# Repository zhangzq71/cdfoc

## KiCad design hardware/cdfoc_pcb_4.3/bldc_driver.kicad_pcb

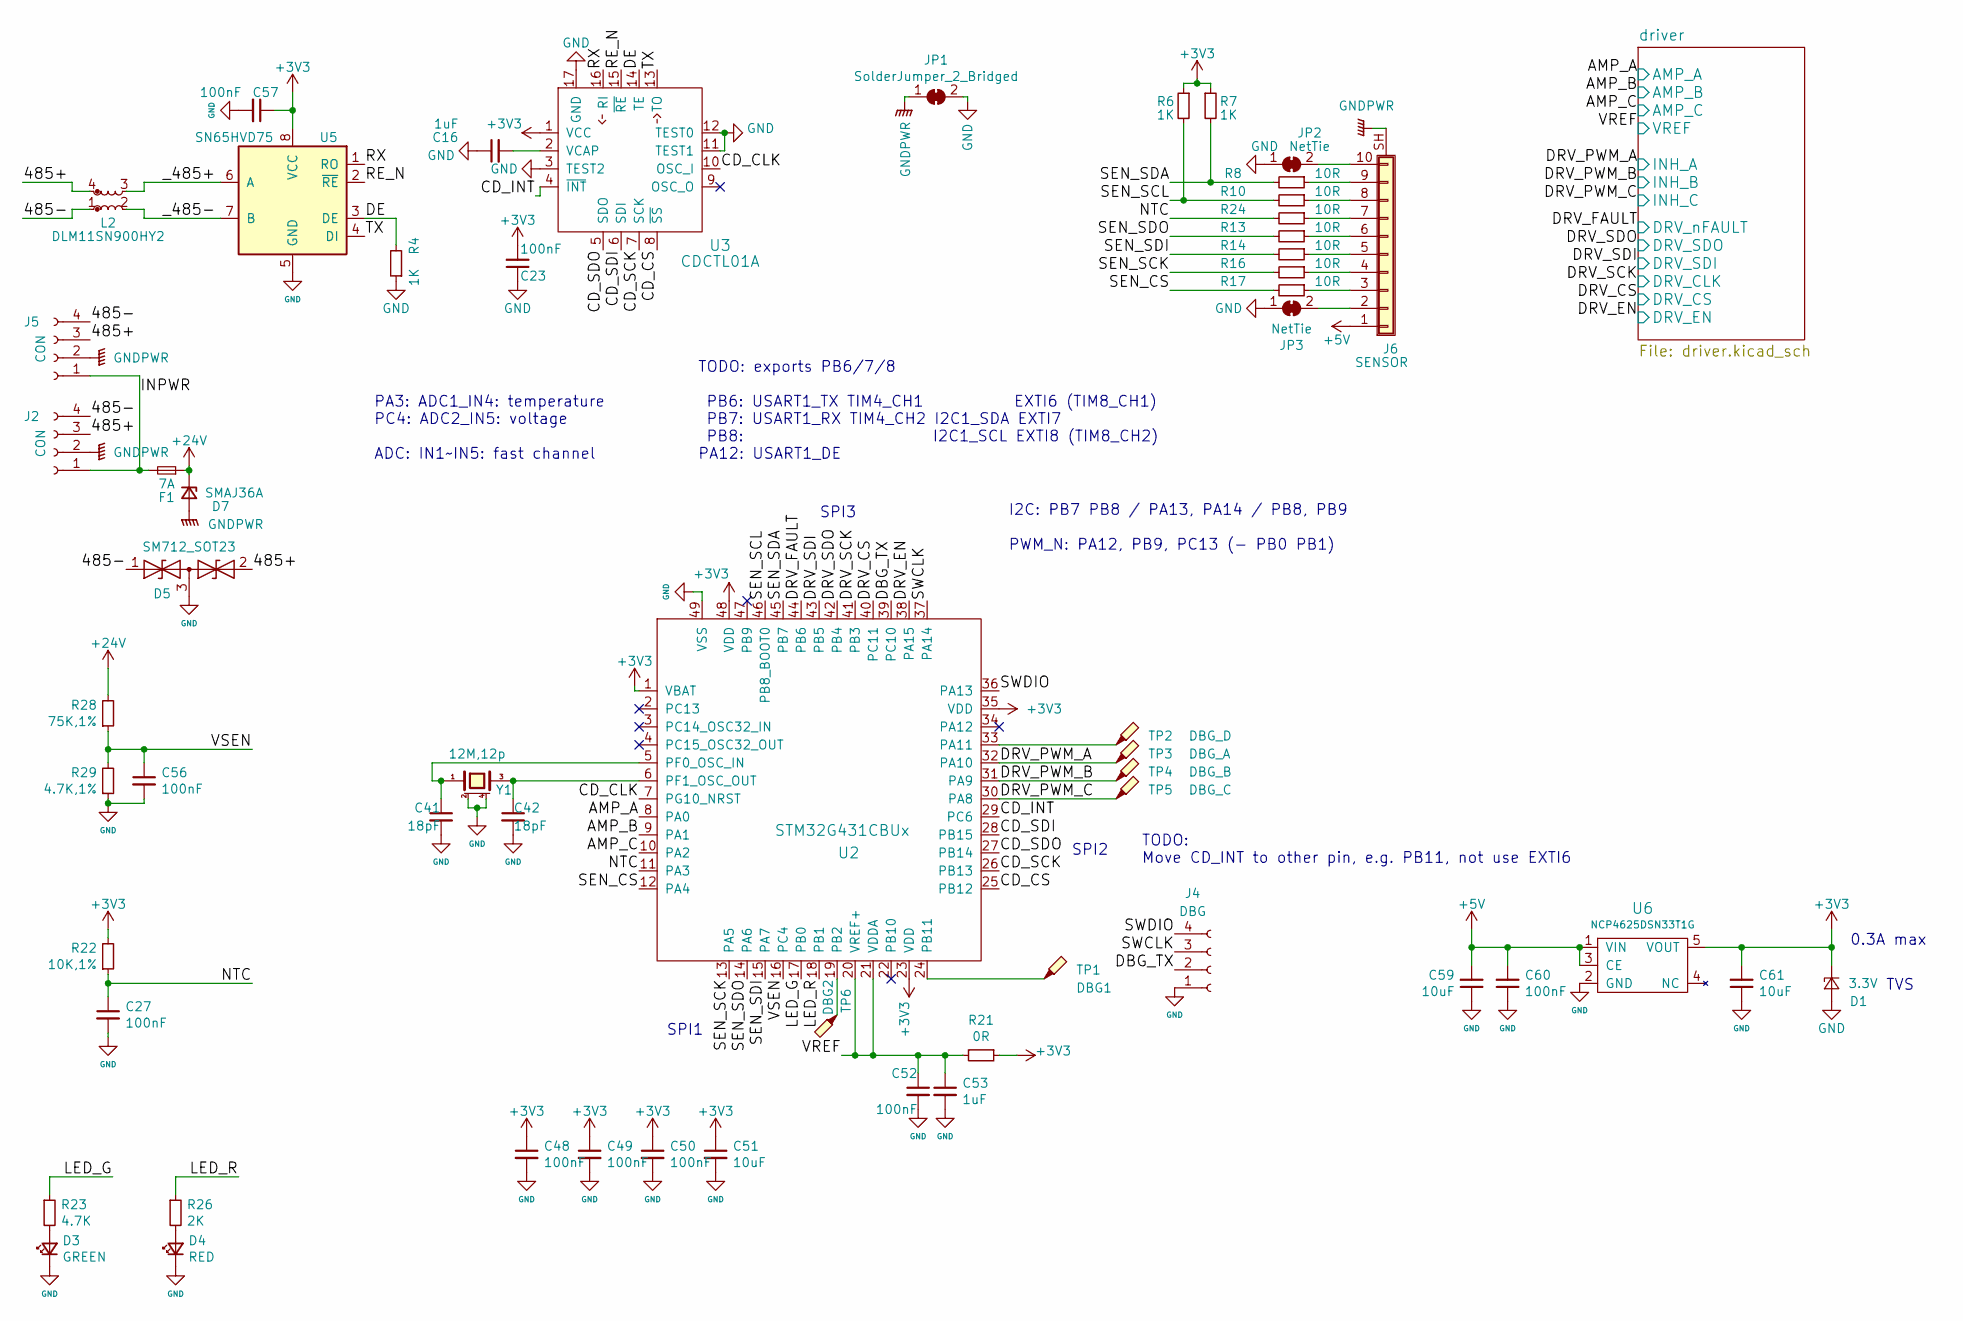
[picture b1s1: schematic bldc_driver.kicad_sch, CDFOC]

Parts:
C16, C53: 1uF; 0402
C23, C27, C48, C49, C50, C52, C56, C57, C60: 100nF; 0402
C41, C42: 18pF; 0402
C51, C59, C61: 10uF; 0402C_BIG
D1: 3.3V; SOD-923
D3: GREEN; 0402D
D4: RED; 0402D
D5: SM712_SOT23; SOT-23
D7: SMAJ36A; SMA
F1: 7A; 1206R
J2, J5: CON; CONN_5268-04A_1x04_P2.50mm_H
J4: DBG; PAD_DIP_4P_1mm
J6: SENSOR; CONN_SH1.0mm_10P_HSMD
JP1: SolderJumper_2_Bridged; NetTie-2_SMD_Pad1mm
JP2, JP3: NetTie; NetTie-2_SMD_Pad0.5mm
L2: DLM11SN900HY2; L_CommonModeChoke_Coilcraft_0603USB
R4, R6, R7: 1K; 0402
R8, R10, R13, R14, R16, R17, R24: 10R; 0402
R21: 0R; 0402
R22: 10K,1%; 0402
R23: 4.7K; 0402
R26: 2K; 0402
R28: 75K,1%; 0402
R29: 4.7K,1%; 0402
TP1: DBG1; TP-D0.8mm
TP2: DBG_D; TP-D0.8mm
TP3: DBG_A; TP-D0.8mm
TP4: DBG_B; TP-D0.8mm
TP5: DBG_C; TP-D0.8mm
TP6: DBG2; TP-D0.8mm
U2: STM32G431CBUx; QFN-48-1EP_7x7mm_P0.5mm_EP5.6x5.6mm
U3: CDCTL01A; QFN-16-1EP_3x3mm_P0.5mm_EP1.7x1.7mm
U5: SN65HVD75; SON-8
U6: NCP4625DSN33T1G; SOT-23-5
Y1: 12M,12p; XTAL-3225

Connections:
+3V3: C23.2, C48.1, C49.1, C50.1, C51.1, C57.1, C61.2, D1.1 (K), R6.1, R7.1, R21.1, R22.2, U2.1 (VBAT), U2.23 (VDD), U2.35 (VDD), U2.48 (VDD), U3.1 (VCC), U5.8 (VCC), U6.5 (VOUT); also elsewhere on the board
+5V: C59.2, C60.2, J6.1, U6.1 (VIN), U6.3 (CE); also elsewhere on the board
+24V: D7.1 (K), F1.1, R28.2; also elsewhere on the board
/485+: D5.2 (A2), J2.3, J5.3, L2.4
/485-: D5.1 (A1), J2.4, J5.4, L2.1
/AMP_A: U2.8 (PA0); also elsewhere on the board
/AMP_B: U2.9 (PA1); also elsewhere on the board
/AMP_C: U2.10 (PA2); also elsewhere on the board
/CD_CLK: U2.7 (PG10_NRST), U3.10 (OSC_I)
/CD_CS: U2.25 (PB12), U3.8 (~SS)
/CD_INT: U2.29 (PC6), U3.4 (~INT)
/CD_SCK: U2.26 (PB13), U3.7 (SCK)
/CD_SDI: U2.28 (PB15), U3.6 (SDI)
/CD_SDO: U2.27 (PB14), U3.5 (SDO)
/DBG_TX: J4.2, U2.39 (PC10)
/DE: R4.2, U3.14 (TE), U5.3 (DE)
/DRV_CS: U2.40 (PC11); also elsewhere on the board
/DRV_EN: U2.38 (PA15); also elsewhere on the board
/DRV_FAULT: U2.44 (PB6); also elsewhere on the board
/DRV_PWM_A: TP3.1, U2.32 (PA10); also elsewhere on the board
/DRV_PWM_B: TP4.1, U2.31 (PA9); also elsewhere on the board
/DRV_PWM_C: TP5.1, U2.30 (PA8); also elsewhere on the board
/DRV_SCK: U2.41 (PB3); also elsewhere on the board
/DRV_SDI: U2.43 (PB5); also elsewhere on the board
/DRV_SDO: U2.42 (PB4); also elsewhere on the board
/INPWR: F1.2, J2.1, J5.1
/LED_G: R23.1, U2.17 (PB0)
/LED_R: R26.1, U2.18 (PB1)
/NTC: C27.1, R22.1, R24.2, U2.11 (PA3)
/RE_N: U3.15 (~RE), U5.2 (~RE)
/RX: U3.16 (RI), U5.1 (RO)
/SEN_CS: R17.2, U2.12 (PA4)
/SEN_SCK: R16.2, U2.13 (PA5)
/SEN_SCL: R6.2, R10.2, U2.46 (PB8_BOOT0)
/SEN_SDA: R7.2, R8.2, U2.45 (PB7)
/SEN_SDI: R14.2, U2.15 (PA7)
/SEN_SDO: R13.2, U2.14 (PA6)
/SWCLK: J4.3, U2.37 (PA14)
/SWDIO: J4.4, U2.36 (PA13)
/TX: U3.13 (TO), U5.4 (DI)
/VREF: C52.1, C53.1, R21.2, U2.20 (VREF+), U2.21 (VDDA); also elsewhere on the board
/VSEN: C56.1, R28.1, R29.2, U2.16 (PC4)
/_485+: L2.3, U5.6 (A)
/_485-: L2.2, U5.7 (B)
GND: C16.1, C23.1, C27.2, C41.2, C42.2, C48.2, C49.2, C50.2, C51.2, C52.2, C53.2, C56.2, C57.2, C59.1, C60.1, C61.1, D1.2 (A), D3.1 (K), D4.1 (K), D5.3 (common), J4.1, JP1.2 (B), JP2.1 (A), JP3.1 (A), R4.1, R29.1, U2.49 (VSS), U3.3 (TEST2), U3.11 (TEST1), U3.12 (TEST0), U3.17 (GND), U5.5 (GND), U6.2 (GND), Y1.2 (case), Y1.4 (case); also elsewhere on the board
GNDPWR: D7.2 (A), J2.2, J5.2, J6.SH (Shield), JP1.1 (A); also elsewhere on the board
unnamed: D3.2 (A), R23.2
unnamed: D4.2 (A), R26.2
unnamed: J6.2, JP3.2 (B)
unnamed: J6.3, R17.1
unnamed: J6.4, R16.1
unnamed: J6.5, R14.1
unnamed: J6.6, R13.1
unnamed: J6.7, R24.1
unnamed: J6.8, R10.1
unnamed: J6.9, R8.1
unnamed: J6.10, JP2.2 (B)
unnamed: TP2.1, U2.33 (PA11)
unnamed: TP6.1, U2.19 (PB2)
unnamed: TP1.1, U2.24 (PB11)
unnamed: C41.1, U2.5 (PF0_OSC_IN), Y1.1
unnamed: C42.1, U2.6 (PF1_OSC_OUT), Y1.3
unnamed: C16.2, U3.2 (VCAP)

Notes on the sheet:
PA3: ADC1_IN4: temperature PC4: ADC2_IN5: voltage ADC: IN1~IN5: fast channel
TODO: Move CD_INT to other pin, e.g. PB11, not use EXTI6
TODO: exports PB6/7/8 PB6: USART1_TX TIM4_CH1 EXTI6 (TIM8_CH1) PB7: USART1_RX TIM4_CH2 I2C1_SDA EXTI7 PB8: I2C1_SCL EXTI8 (TIM8_CH2) PA12: USART1_DE
SPI3
SPI1
TVS
I2C: PB7 PB8 / PA13, PA14 / PB8, PB9 PWM_N: PA12, PB9, PC13 (- PB0 PB1)
0.3A max
SPI2

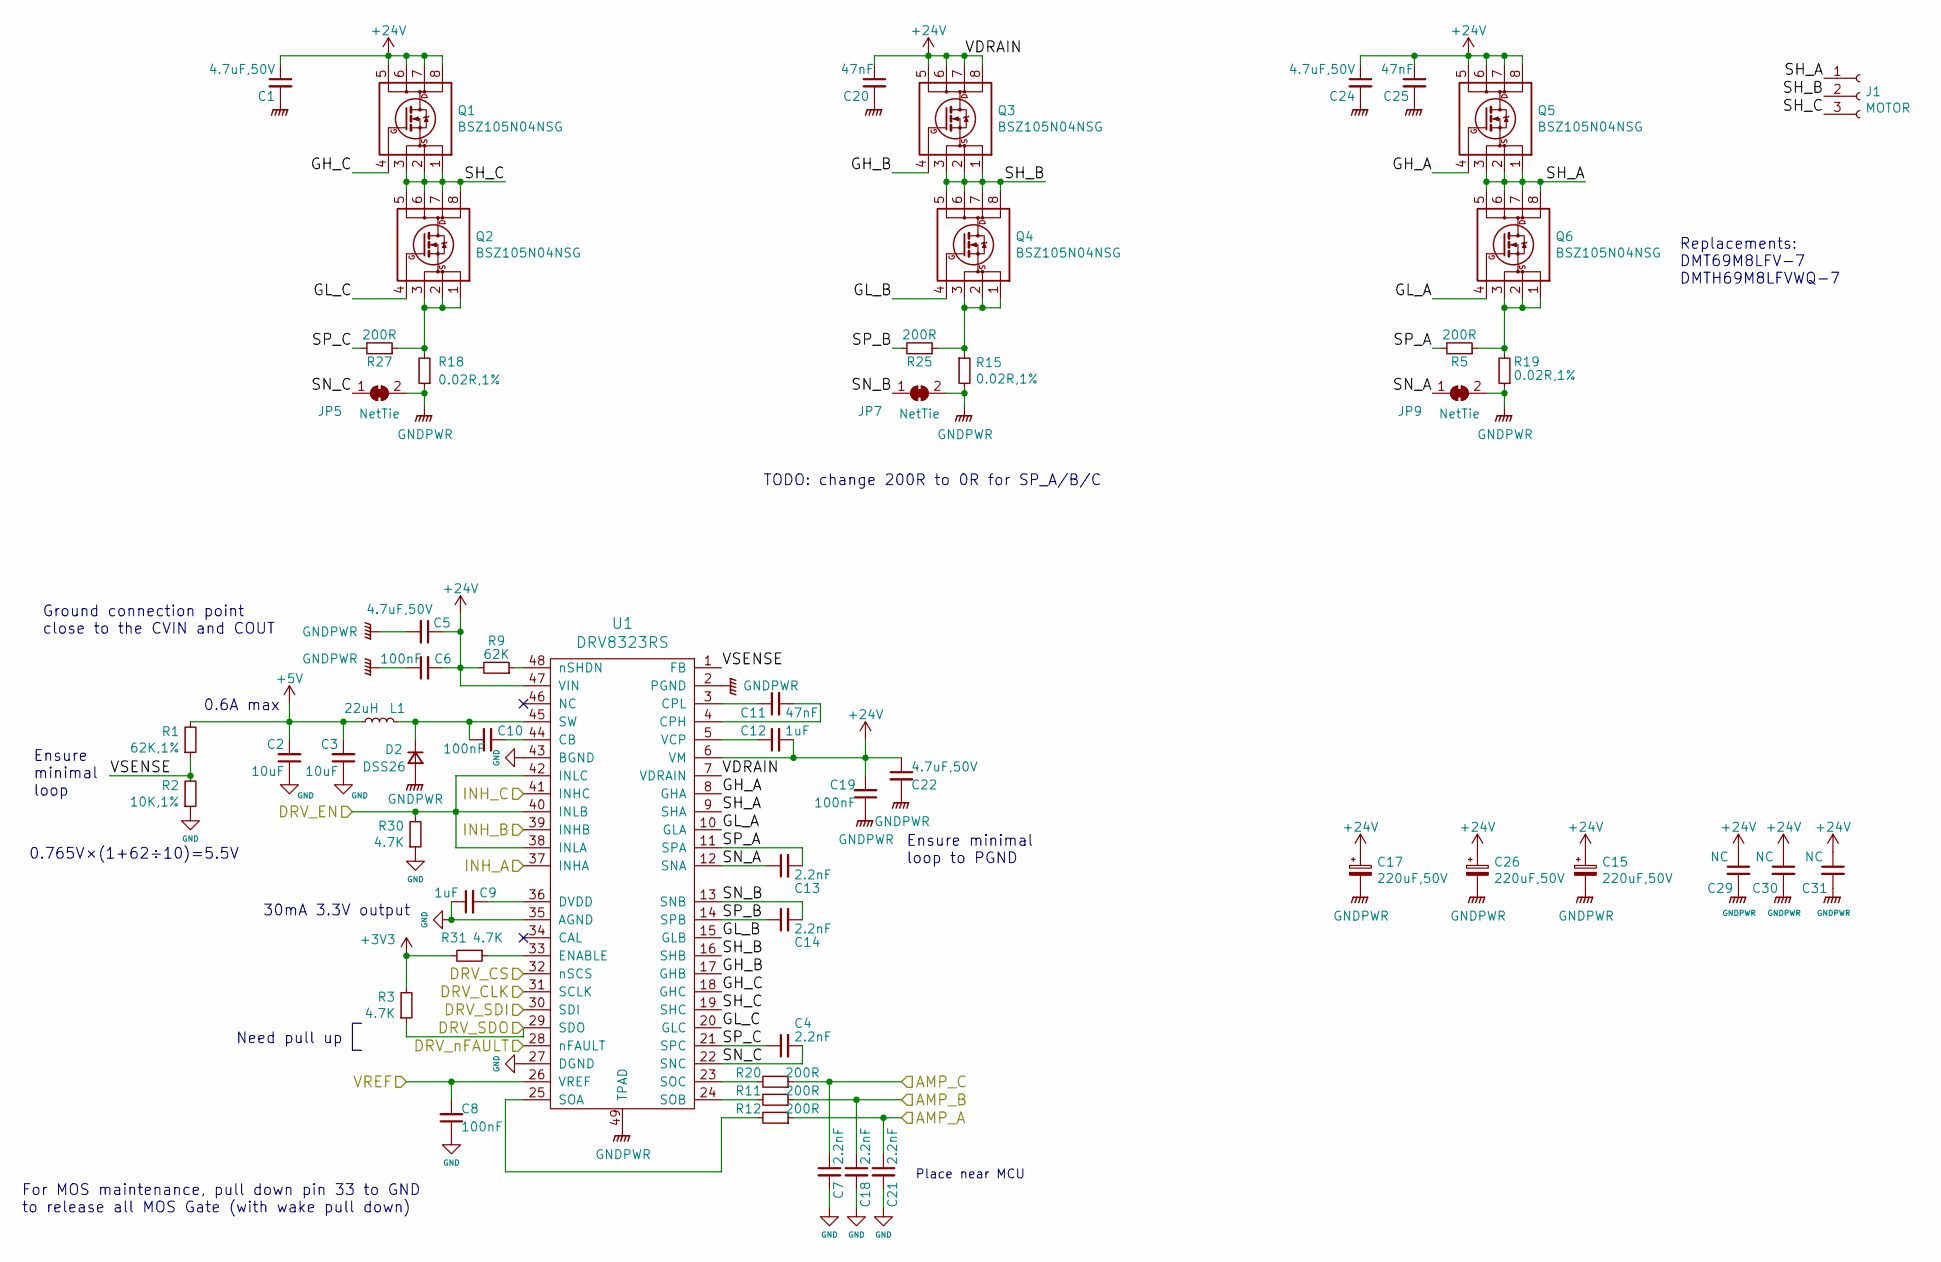
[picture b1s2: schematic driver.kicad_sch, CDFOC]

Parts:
C1, C5, C22, C24: 4.7uF,50V; 0805
C2, C3: 10uF; 0402C_BIG
C4, C7, C13, C14, C18, C21: 2.2nF; 0402
C6, C8, C10, C19: 100nF; 0402
C9, C12: 1uF; 0402
C11, C20, C25: 47nF; 0402
C15, C17, C26: 220uF,50V; CP_Elec_10x10
C29, C30, C31: NC; 1206
D2: DSS26; D_SOD-123F
J1: MOTOR; CONN_5268-03A_1x03_P2.50mm_H
JP5, JP7, JP9: NetTie; NetTie-2_SMD_Pad0.16mm
L1: 22uH; L_Taiyo-Yuden_MD-4040
Q1, Q2, Q3, Q4, Q5, Q6: BSZ105N04NSG; PG-TSDSON-8_3x3mm
R1: 62K,1%; 0402
R2: 10K,1%; 0402
R3, R30, R31: 4.7K; 0402
R5, R11, R12, R20, R25, R27: 200R; 0402
R9: 62K; 0402
R15, R18, R19: 0.02R,1%; 1206R
U1: DRV8323RS; QFN-48-1EP_7x7mm_P0.5mm_EP5.15x5.15mm

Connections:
+3V3: R3.2, R31.2; also elsewhere on the board
+5V: C2.2, C3.2, L1.1, R1.2; also elsewhere on the board
+24V: C1.1, C5.1, C6.2, C12.2, C15.1, C17.1, C19.2, C20.1, C22.1, C24.1, C25.1, C26.1, C29.1, C30.1, C31.1, Q1.5 (D), Q1.6 (D), Q1.7 (D), Q1.8 (D), Q3.5 (D), Q3.6 (D), Q3.7 (D), Q3.8 (D), Q5.5 (D), Q5.6 (D), Q5.7 (D), Q5.8 (D), R9.2, U1.6 (VM), U1.7 (VDRAIN), U1.47 (VIN); also elsewhere on the board
/AMP_A: C21.1, R12.1; also elsewhere on the board
/AMP_B: C18.1, R11.1; also elsewhere on the board
/AMP_C: C7.1, R20.1; also elsewhere on the board
/DRV_CS: U1.32 (nSCS); also elsewhere on the board
/DRV_EN: R30.2, U1.38 (INLA), U1.40 (INLB), U1.42 (INLC); also elsewhere on the board
/DRV_FAULT: U1.28 (nFAULT); also elsewhere on the board
/DRV_PWM_A: U1.37 (INHA); also elsewhere on the board
/DRV_PWM_B: U1.39 (INHB); also elsewhere on the board
/DRV_PWM_C: U1.41 (INHC); also elsewhere on the board
/DRV_SCK: U1.31 (SCLK); also elsewhere on the board
/DRV_SDI: U1.30 (SDI); also elsewhere on the board
/DRV_SDO: R3.1, U1.29 (SDO); also elsewhere on the board
/VREF: C8.2, U1.26 (VREF); also elsewhere on the board
/driver/GH_A: Q5.4 (G), U1.8 (GHA)
/driver/GH_B: Q3.4 (G), U1.17 (GHB)
/driver/GH_C: Q1.4 (G), U1.18 (GHC)
/driver/GL_A: Q6.4 (G), U1.10 (GLA)
/driver/GL_B: Q4.4 (G), U1.15 (GLB)
/driver/GL_C: Q2.4 (G), U1.20 (GLC)
/driver/SH_A: J1.1, Q5.1 (S), Q5.2 (S), Q5.3 (S), Q6.5 (D), Q6.6 (D), Q6.7 (D), Q6.8 (D), U1.9 (SHA)
/driver/SH_B: J1.2, Q3.1 (S), Q3.2 (S), Q3.3 (S), Q4.5 (D), Q4.6 (D), Q4.7 (D), Q4.8 (D), U1.16 (SHB)
/driver/SH_C: J1.3, Q1.1 (S), Q1.2 (S), Q1.3 (S), Q2.5 (D), Q2.6 (D), Q2.7 (D), Q2.8 (D), U1.19 (SHC)
/driver/SN_A: C13.1, JP9.1 (A), U1.12 (SNA)
/driver/SN_B: C14.2, JP7.1 (A), U1.13 (SNB)
/driver/SN_C: C4.2, JP5.1 (A), U1.22 (SNC)
/driver/SP_A: C13.2, R5.2, U1.11 (SPA)
/driver/SP_B: C14.1, R25.2, U1.14 (SPB)
/driver/SP_C: C4.1, R27.2, U1.21 (SPC)
/driver/VSENSE: R1.1, R2.2, U1.1 (FB)
GND: C2.1, C3.1, C7.2, C8.1, C9.1, C18.2, C21.2, R2.1, R30.1, U1.27 (DGND), U1.35 (AGND), U1.43 (BGND); also elsewhere on the board
GNDPWR: C1.2, C5.2, C6.1, C15.2, C17.2, C19.1, C20.2, C22.2, C24.2, C25.2, C26.2, C29.2, C30.2, C31.2, D2.2 (A), JP5.2 (B), JP7.2 (B), JP9.2 (B), R15.2, R18.1, R19.1, U1.2 (PGND), U1.49 (TPAD); also elsewhere on the board
unnamed: C10.1, D2.1 (K), L1.2, U1.45 (SW)
unnamed: Q2.1 (S), Q2.2 (S), Q2.3 (S), R18.2, R27.1
unnamed: Q4.1 (S), Q4.2 (S), Q4.3 (S), R15.1, R25.1
unnamed: Q6.1 (S), Q6.2 (S), Q6.3 (S), R5.1, R19.2
unnamed: C10.2, U1.44 (CB)
unnamed: C11.2, U1.4 (CPH)
unnamed: C11.1, U1.3 (CPL)
unnamed: C9.2, U1.36 (DVDD)
unnamed: R31.1, U1.33 (ENABLE)
unnamed: R12.2, U1.25 (SOA)
unnamed: R11.2, U1.24 (SOB)
unnamed: R20.2, U1.23 (SOC)
unnamed: C12.1, U1.5 (VCP)
unnamed: R9.1, U1.48 (nSHDN)

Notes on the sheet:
Ground connection point close to the CVIN and COUT
Need pull up
For MOS maintenance, pull down pin 33 to GND to release all MOS Gate (with wake pull down)
Replacements: DMT69M8LFV-7 DMTH69M8LFVWQ-7
30mA 3.3V output
Ensure minimal loop to PGND
TODO: change 200R to 0R for SP_A/B/C
0.765V×(1+62÷10)=5.5V
0.6A max
Place near MCU
Ensure minimal loop

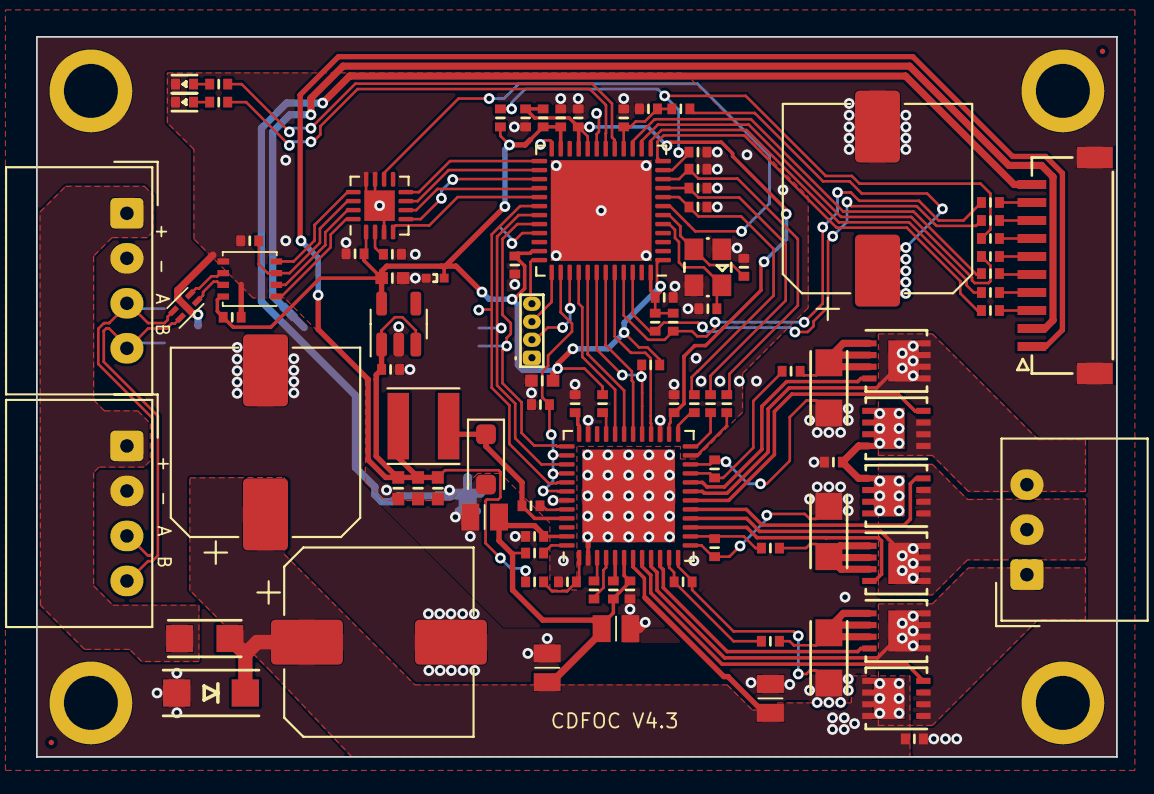
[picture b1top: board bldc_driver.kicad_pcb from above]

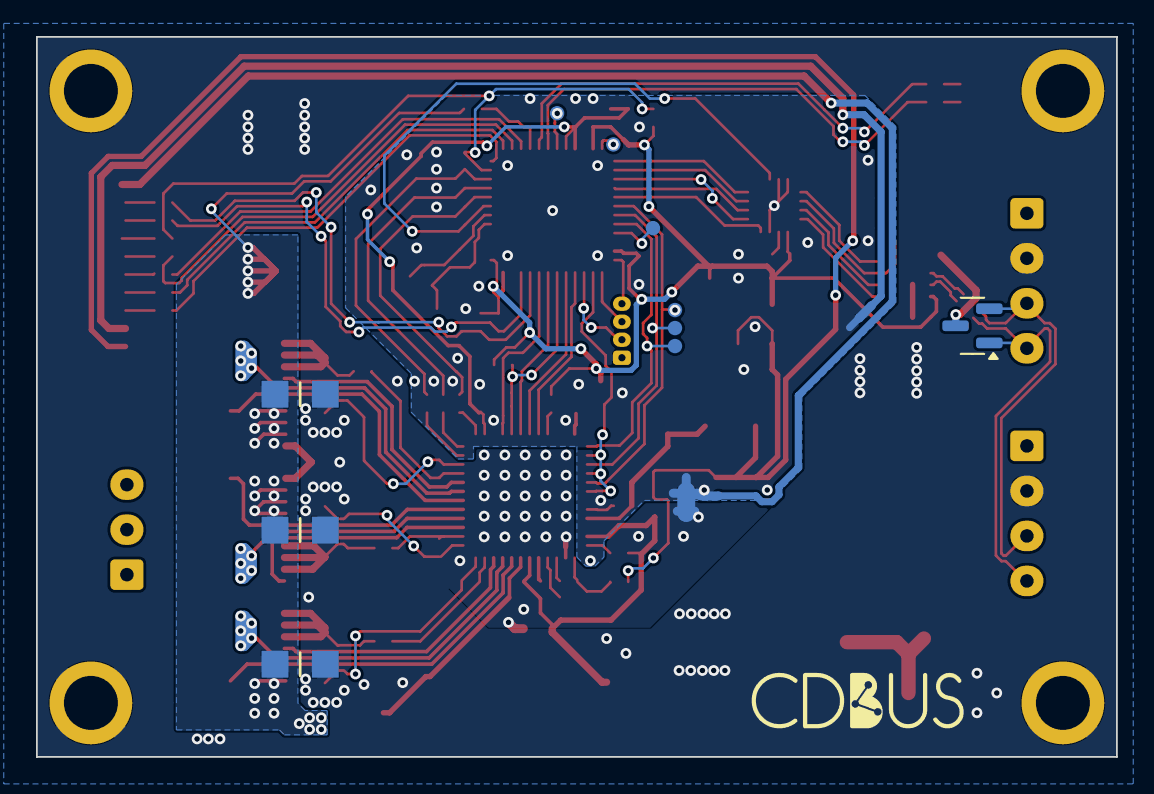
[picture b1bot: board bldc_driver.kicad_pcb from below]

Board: 2 copper layers, 60.0 x 40.0 mm, 116 parts (13 on the bottom side), 93 nets.

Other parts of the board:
J11, J12, J13, J14: Hole; Hole-TH-3.2mm_4mm

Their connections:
GNDPWR: J11.1, J12.1, J13.1, J14.1; also elsewhere on the board

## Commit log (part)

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2026-05-29 加入两个程序， python sine_wave_ctrl.py --dev COM37 --baud 30000000 --mode pos --amplitude 200000 --duration 0 --freq 1.0 --rate 500, python sine_wave_ctrl.py --dev COM37 --mode tp --rpm 100 --dir cw --dura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
2026-05-29 加入 speed 模式
2026-05-29 这个版本才正确
2026-05-29 add hw
